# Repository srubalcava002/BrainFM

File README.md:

# BrainFM

A wireless bone conduction headset based on the ESP32, designed to fit inside of a hat. Powered by an ESP32 and an off the shelf DAC with built-in amplifier (MAX98357).
## PCB Images

## Physical Build

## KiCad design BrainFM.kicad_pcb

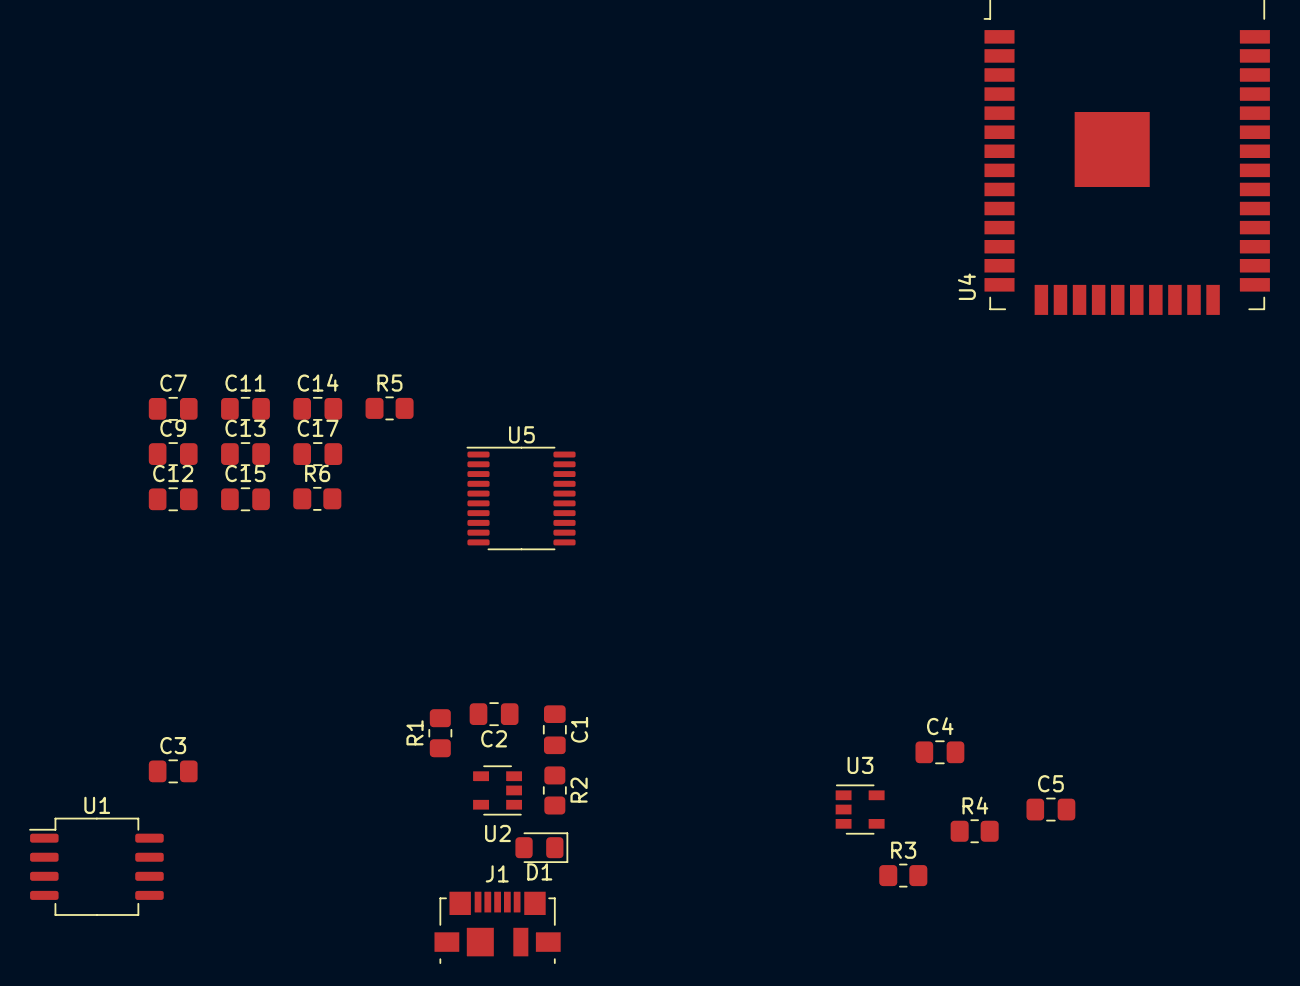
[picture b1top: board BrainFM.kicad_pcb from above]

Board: 2 copper layers, 26 parts (0 on the bottom side), 20 nets, no tracks yet.

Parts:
C1, C2, C3, C4, C5: 4.7 uf; C_0805_2012Metric_Pad1.18x1.45mm_HandSolder
C7, C9, C11: .1 uf; C_0805_2012Metric_Pad1.18x1.45mm_HandSolder
C12, C13: 2.2 uf; C_0805_2012Metric_Pad1.18x1.45mm_HandSolder
C14: 0.1 uf; C_0805_2012Metric_Pad1.18x1.45mm_HandSolder
C15, C17: 2.2 nf; C_0805_2012Metric_Pad1.18x1.45mm_HandSolder
D1: LED; LED_0805_2012Metric_Pad1.15x1.40mm_HandSolder
J1: USB_B_Micro; USB_Micro-B_Molex_47346-0001
R1, R4: 2k; R_0805_2012Metric_Pad1.20x1.40mm_HandSolder
R2, R5, R6: 470; R_0805_2012Metric_Pad1.20x1.40mm_HandSolder
R3: 10k; R_0805_2012Metric_Pad1.20x1.40mm_HandSolder
U1: PAM8302AAD; SO-8_5.3x6.2mm_P1.27mm
U2: MCP73831-2-OT; SOT-23-5
U3: TLV75801PDBV; SOT-23-5
U4: ESP32-WROOM-32
U5: PCM5102; TSSOP-20_4.4x6.5mm_P0.65mm

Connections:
+3V3: C3.1, C5.1, C7.1, C9.1, C11.2, R3.1, U1.1, U1.6, U3.5, U4.2, U5.1, U5.8, U5.17, U5.20
-BATT: C1.2, C2.1, C3.2, C4.2, C5.2, C7.2, C9.2, C11.1, C13.1, C14.1, C15.2, C17.1, J1.5, J1.6, R1.2, R4.2, U1.7, U2.2, U3.2, U4.1, U4.15, U4.38, U4.39, U5.3, U5.9, U5.10, U5.11, U5.16, U5.19
LEFT: C15.1, R5.1
unnamed: C1.1, U2.3
unnamed: C2.2, D1.2, J1.1, U2.4
unnamed: C12.1, U5.4
unnamed: C12.2, U5.2
unnamed: C13.2, U5.5
unnamed: C14.2, U5.18
unnamed: D1.1, R2.1
unnamed: R1.1, U2.5
unnamed: R2.2, U2.1
unnamed: R3.2, R4.1, U3.4
unnamed: R5.2, U5.6
unnamed: R6.2, U5.7
unnamed: U4.10, U5.14
unnamed: U4.11, U5.13
unnamed: U4.36, U5.15
RIGHT: C17.2, R6.1
VCC: C4.1, U3.1, U3.3

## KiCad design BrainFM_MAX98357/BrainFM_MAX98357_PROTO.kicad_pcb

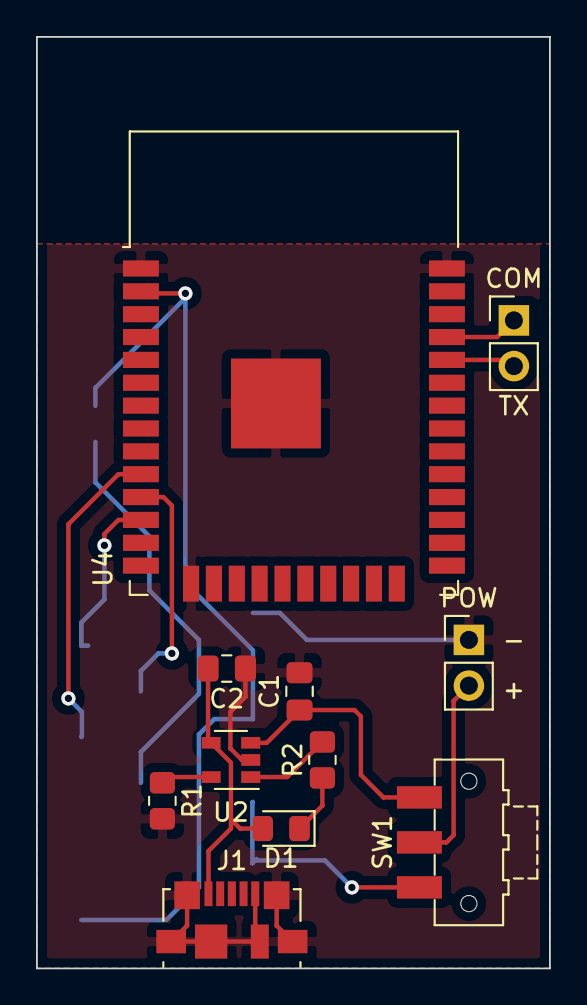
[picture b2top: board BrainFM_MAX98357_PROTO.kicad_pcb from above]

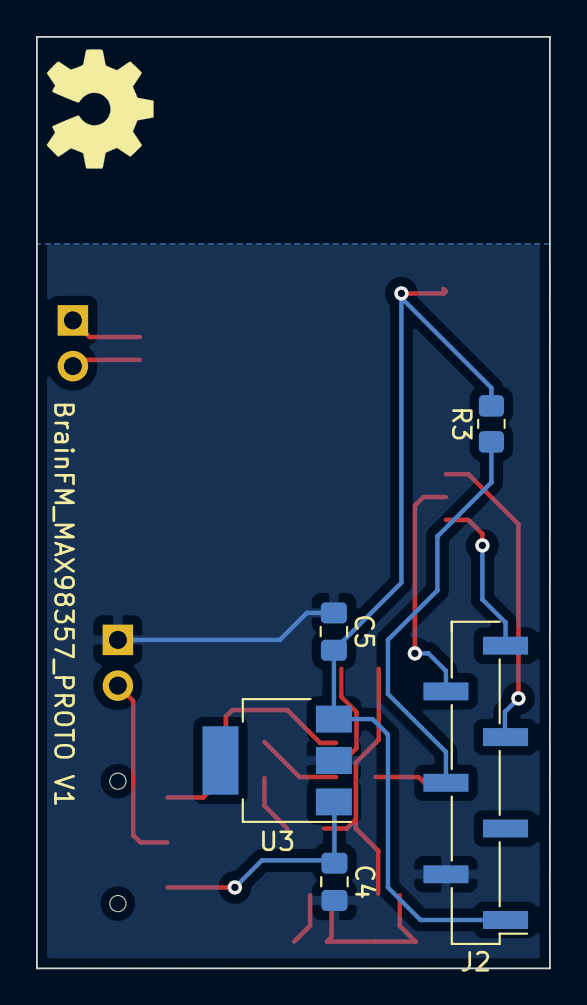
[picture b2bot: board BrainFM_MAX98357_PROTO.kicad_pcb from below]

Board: 2 copper layers, 28.5 x 51.8 mm, 16 parts (5 on the bottom side), 14 nets.

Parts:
C1, C2, C4, C5: 4.7 uf; C_0805_2012Metric_Pad1.18x1.45mm_HandSolder
COM: PinHeader_1x02_P2.54mm_Vertical
D1: LED; LED_0805_2012Metric_Pad1.15x1.40mm_HandSolder
J1: USB_B_Micro; USB_Micro-B_Molex_47346-0001
J2: Conn_01x07_Male; PinHeader_1x07_P2.54mm_Vertical_SMD_Pin1Left
POW: PinHeader_1x02_P2.54mm_Vertical
R1: 2k; R_0805_2012Metric_Pad1.20x1.40mm_HandSolder
R2: 470; R_0805_2012Metric_Pad1.20x1.40mm_HandSolder
R3: 10k; R_0805_2012Metric_Pad1.20x1.40mm_HandSolder
SW1: SW_SPDT_CK-JS102011SAQN
U2: MCP73831-2-OT; SOT-23-5
U3: TC1262-33; SOT-223
U4: ESP32-WROOM-32

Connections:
+3V3: C5.2, J2.1, R3.2, U3.3, U4.2
-BATT: C1.2, C2.1, C4.2, C5.1, J1.5, J1.6, J2.2, POW.1, R1.2, U2.2, U3.2, U4.1, U4.15, U4.38, U4.39
BCK: J2.6, U4.11
DATA: J2.5, U4.10
LRCK: J2.7, U4.12
unnamed: C1.1, SW1.3, U2.3
unnamed: C2.2, D1.2, J1.1, U2.4
unnamed: D1.1, R2.1
unnamed: J2.4, R3.1
unnamed: R1.1, U2.5
unnamed: R2.2, U2.1
P_RX: COM.1, U4.35
P_TX: COM.2, U4.34
VCC: C4.1, POW.2, SW1.1, SW1.2, U3.1

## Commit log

2020-08-04 start pcb layout
2020-08-04 add README.md
2020-11-16 work on PCM5012
2020-12-15 update schematic and layout
2020-12-20 start pcb layout on bottom layer
2021-06-09 backup before change to TC1262
2021-06-09 update pcb layout
2021-06-09 change TLV75801 for TC1262
2021-06-09 drc runs clean
2021-06-18 sent to osh park
2021-09-23 update with working design
2022-01-30 add images
2023-10-02 add image
